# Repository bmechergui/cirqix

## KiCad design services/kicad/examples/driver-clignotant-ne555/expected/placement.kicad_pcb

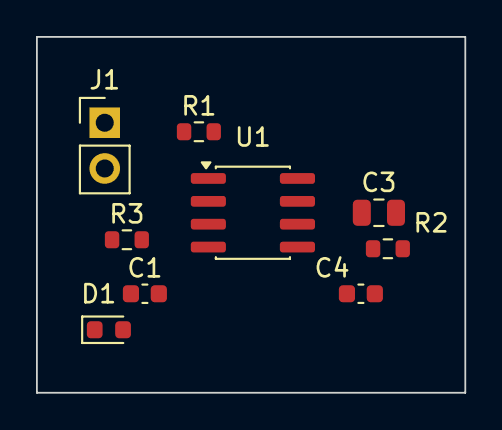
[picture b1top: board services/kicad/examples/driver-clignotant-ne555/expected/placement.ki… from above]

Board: 2 copper layers, 23.8 x 19.8 mm, 9 parts (0 on the bottom side), 7 nets, no tracks yet.

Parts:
C1: 100nF; C_0603_1608Metric
C3: 4.7uF; C_0805_2012Metric
C4: 10nF; C_0603_1608Metric
D1: LED_RED; LED_0603_1608Metric
J1: PWR_5V; PinHeader_1x02_P2.54mm_Vertical
R1: 10k; R_0603_1608Metric
R2: 100k; R_0603_1608Metric
R3: 330R; R_0603_1608Metric
U1: NE555; SOIC-8_3.9x4.9mm_P1.27mm

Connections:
CTRL: C4.1, U1.5
DISCH: R1.2, R2.1, U1.7
GND: C1.2, C3.2, C4.2, D1.1, J1.2, U1.1
LED_A: D1.2, R3.2
OUT: R3.1, U1.3
THRES: C3.1, R2.2, U1.2, U1.6
VCC: C1.1, J1.1, R1.1, U1.4, U1.8

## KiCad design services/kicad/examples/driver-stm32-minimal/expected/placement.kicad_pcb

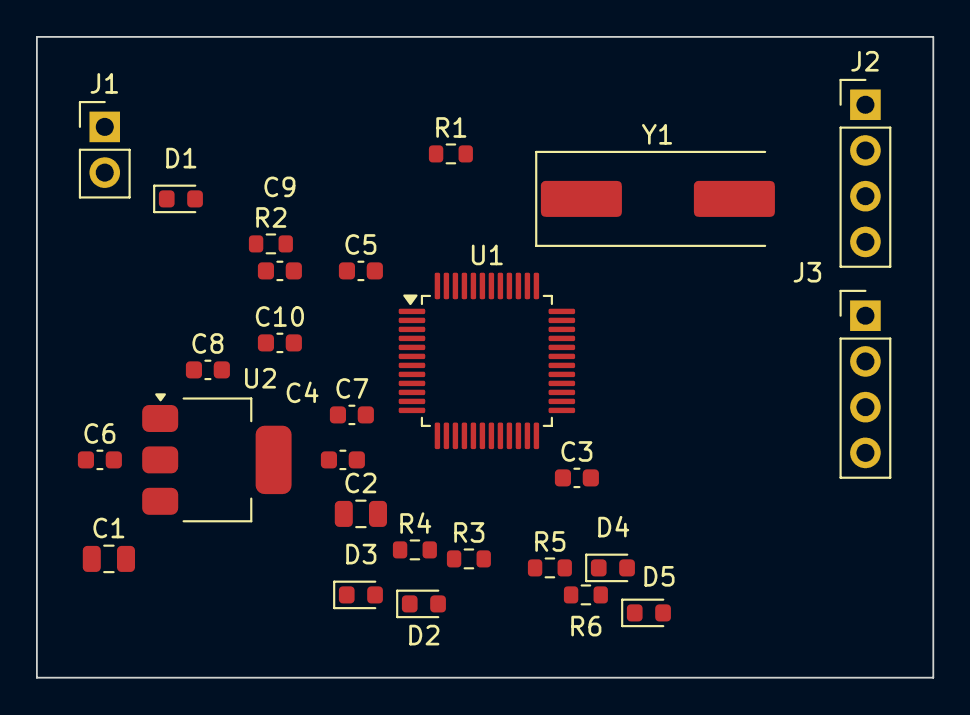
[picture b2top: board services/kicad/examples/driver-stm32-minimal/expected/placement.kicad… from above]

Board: 2 copper layers, 49.8 x 35.6 mm, 27 parts (0 on the bottom side), 22 nets, no tracks yet.

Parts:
C1, C2: 10uF; C_0805_2012Metric
C3, C4, C5, C6, C7, C8: 100nF; C_0603_1608Metric
C9, C10: 20pF; C_0603_1608Metric
D1: LED_GREEN; LED_0603_1608Metric
D2, D3, D4, D5: LED_RED; LED_0603_1608Metric
J1: PWR_5V; PinHeader_1x02_P2.54mm_Vertical
J2: SWD; PinHeader_1x04_P2.54mm_Vertical
J3: UART1; PinHeader_1x04_P2.54mm_Vertical
R1: 10k; R_0603_1608Metric
R2, R3, R4, R5, R6: 470R; R_0603_1608Metric
U1: STM32F103C8T6; LQFP-48_7x7mm_P0.5mm
U2: AMS1117-3.3; SOT-223-3_TabPin2
Y1: 8MHz; Crystal_SMD_HC49-SD

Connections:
+3V3: C2.1, C3.1, C4.1, C5.1, C6.1, C7.1, J2.1, J3.1, U1.1, U1.9, U1.24, U2.2
+5V: C1.1, J1.1, U2.3
BOOT0: R1.1, U1.44
D1_A: D1.2, R2.2
D2_A: D2.2, R3.2
D3_A: D3.2, R4.2
D4_A: D4.2, R5.2
D5_A: D5.2, R6.2
GND: C1.2, C2.2, C3.2, C4.2, C5.2, C6.2, C7.2, C8.2, C9.2, C10.2, D1.1, D2.1, D3.1, D4.1, D5.1, J1.2, J2.4, J3.4, R1.2, U1.8, U1.23, U1.35, U1.47, U2.1
LED_PB0: R3.1, U1.18
LED_PB1: R4.1, U1.19
LED_PB10: R5.1, U1.21
LED_PB11: R6.1, U1.22
LED_PC13: R2.1, U1.2
NRST: C8.1, U1.7
OSC_IN: C9.1, U1.5, Y1.1
OSC_OUT: C10.1, U1.6, Y1.2
PWR_FLAG: U1.36, U1.48
SWCLK: J2.3, U1.37
SWDIO: J2.2, U1.34
UART1_RX: J3.3, U1.31
UART1_TX: J3.2, U1.30

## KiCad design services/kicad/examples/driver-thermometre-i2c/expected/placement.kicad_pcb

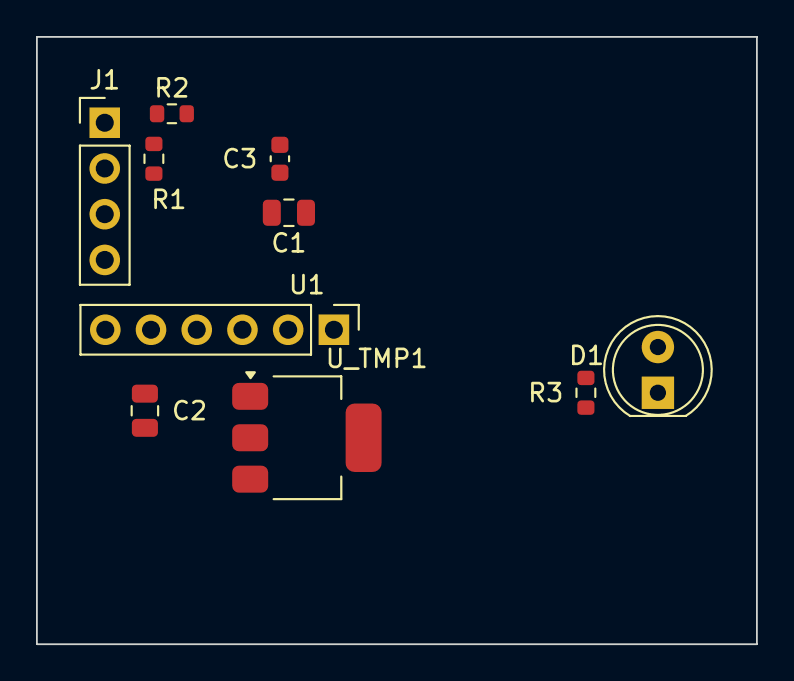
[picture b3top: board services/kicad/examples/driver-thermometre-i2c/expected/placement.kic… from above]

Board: 2 copper layers, 40.0 x 33.7 mm, 10 parts (0 on the bottom side), 6 nets, no tracks yet.

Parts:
C1, C2: 10uF; C_0805_2012Metric
C3: 100nF; C_0603_1608Metric
D1: LED_GREEN; LED_D5.0mm
J1: 5V_GND_SDA_SCL; PinHeader_1x04_P2.54mm_Vertical
R1, R2: 4.7k; R_0603_1608Metric
R3: 1k; R_0603_1608Metric
U1: AMS1117-3.3; SOT-223-3_TabPin2
U_TMP1: TMP102; PinHeader_1x06_P2.54mm_Vertical

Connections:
+3V3: C2.1, C3.1, R1.1, R2.1, R3.1, U_TMP1.5
+5V: C1.1, J1.1
GND: C1.2, C2.2, C3.2, D1.2, J1.2, U1.1, U_TMP1.2, U_TMP1.4
NET_R3_D1: D1.1, R3.2
SCL: J1.4, R2.2, U_TMP1.1
SDA: J1.3, R1.2, U_TMP1.6

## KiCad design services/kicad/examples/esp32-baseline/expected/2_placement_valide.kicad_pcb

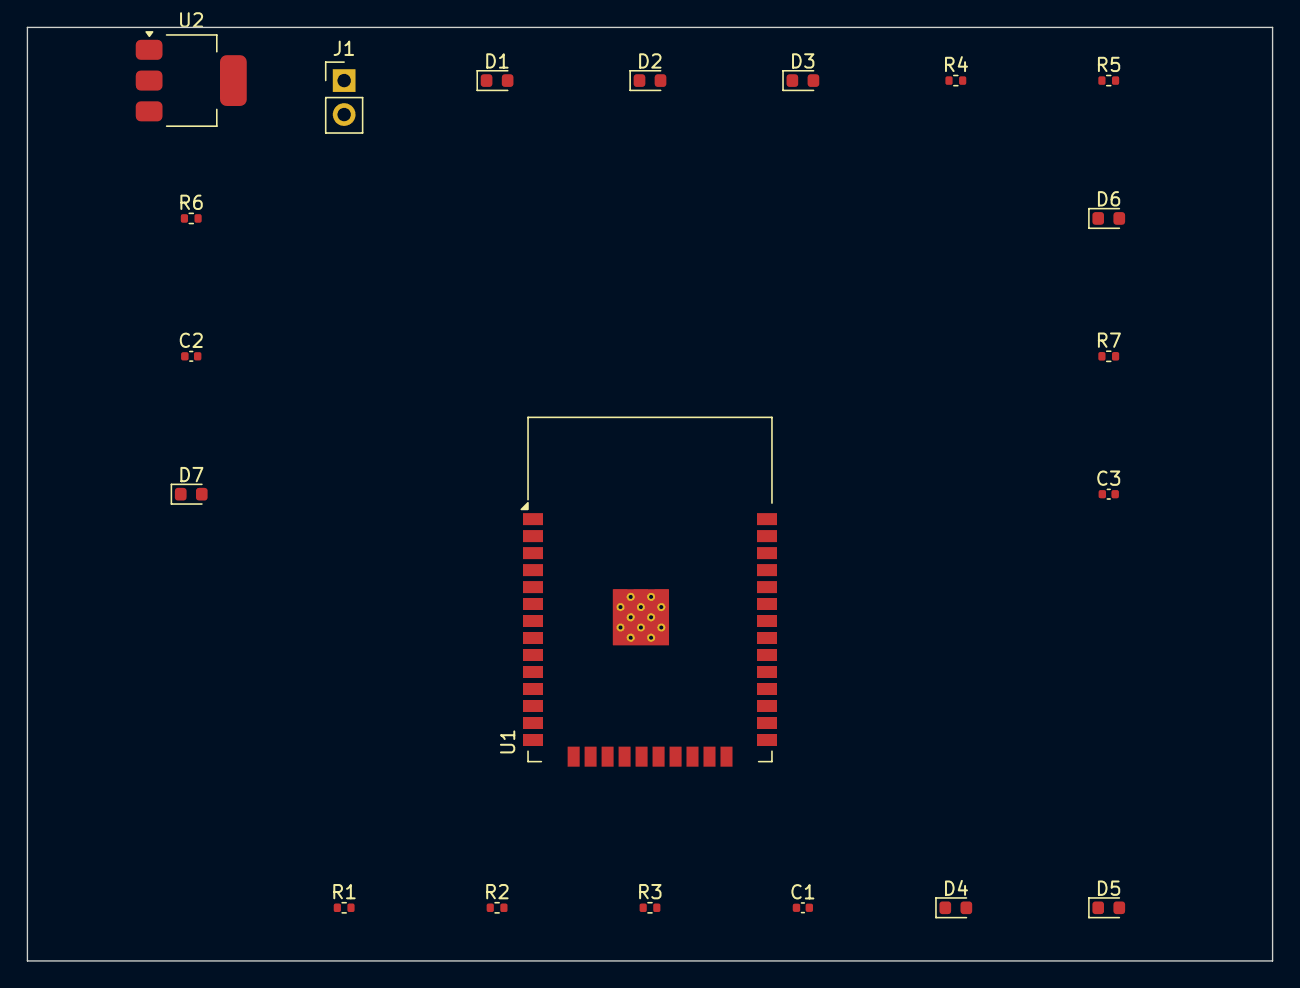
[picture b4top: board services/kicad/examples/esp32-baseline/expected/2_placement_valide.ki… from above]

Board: 2 copper layers, 93.1 x 69.8 mm, 20 parts (0 on the bottom side), 16 nets, no tracks yet.

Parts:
C1, C2, C3: 100nF; C_0402_1005Metric
D1, D2, D3, D4, D5, D6, D7: LED; LED_0603_1608Metric
J1: 5V; PinHeader_1x02_P2.54mm_Vertical
R1, R2, R3, R4, R5, R6, R7: 330; R_0402_1005Metric
U1: ESP32-WROOM-32
U2: AMS1117-3.3; SOT-223-3_TabPin2

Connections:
+3V3: C1.1, C2.1, C3.1, U1.1, U1.15, U1.38, U1.39, U2.2
GND: C1.2, C2.2, C3.2, D1.2, D2.2, D3.2, D4.2, D5.2, D6.2, D7.2, J1.2, U1.8, U2.1
GPIO1: R1.1, U1.10
GPIO2: R2.1, U1.11
GPIO3: R3.1, U1.12
GPIO5: R4.1, U1.13
GPIO6: R5.1, U1.14
GPIO9: R7.1, U1.16
LED1: D1.1, R1.2
LED2: D2.1, R2.2
LED3: D3.1, R3.2
LED5: D4.1, R4.2
LED6: D5.1, R5.2
LED7: D6.1, R6.2
LED9: D7.1, R7.2
VIN: J1.1, U2.3

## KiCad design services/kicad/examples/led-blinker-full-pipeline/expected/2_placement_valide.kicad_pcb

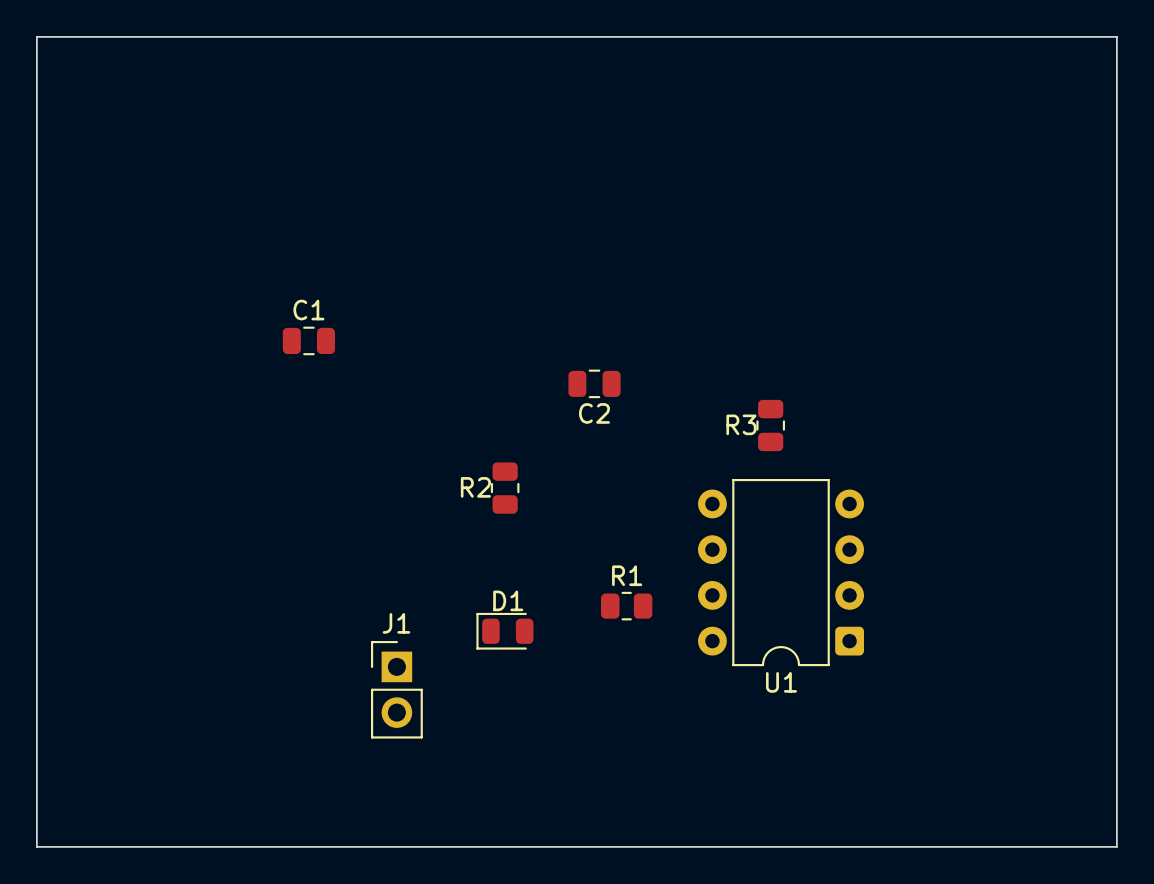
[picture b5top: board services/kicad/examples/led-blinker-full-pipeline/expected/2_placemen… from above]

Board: 2 copper layers, 60.0 x 45.0 mm, 8 parts (0 on the bottom side), 6 nets, no tracks yet.

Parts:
C1: 10uF; C_0805_2012Metric
C2: 100nF; C_0805_2012Metric
D1: LED; LED_0805_2012Metric
J1: Conn_01x02; PinHeader_1x02_P2.54mm_Vertical
R1: 10k; R_0805_2012Metric
R2: 68k; R_0805_2012Metric
R3: 330; R_0805_2012Metric
U1: NE555; DIP-8_W7.62mm

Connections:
DISCH: R1.2, R2.1, U1.7
GND: C1.2, C2.2, D1.2, J1.2, U1.1
LED_A: D1.1, R3.2
OUT: R3.1, U1.3
TRIG_THR: C1.1, R2.2, U1.2, U1.6
VCC: C2.1, J1.1, R1.1, U1.4, U1.8
